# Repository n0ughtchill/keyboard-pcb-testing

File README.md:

# keyboard-pcb-testing

Just learning how to make PCBs

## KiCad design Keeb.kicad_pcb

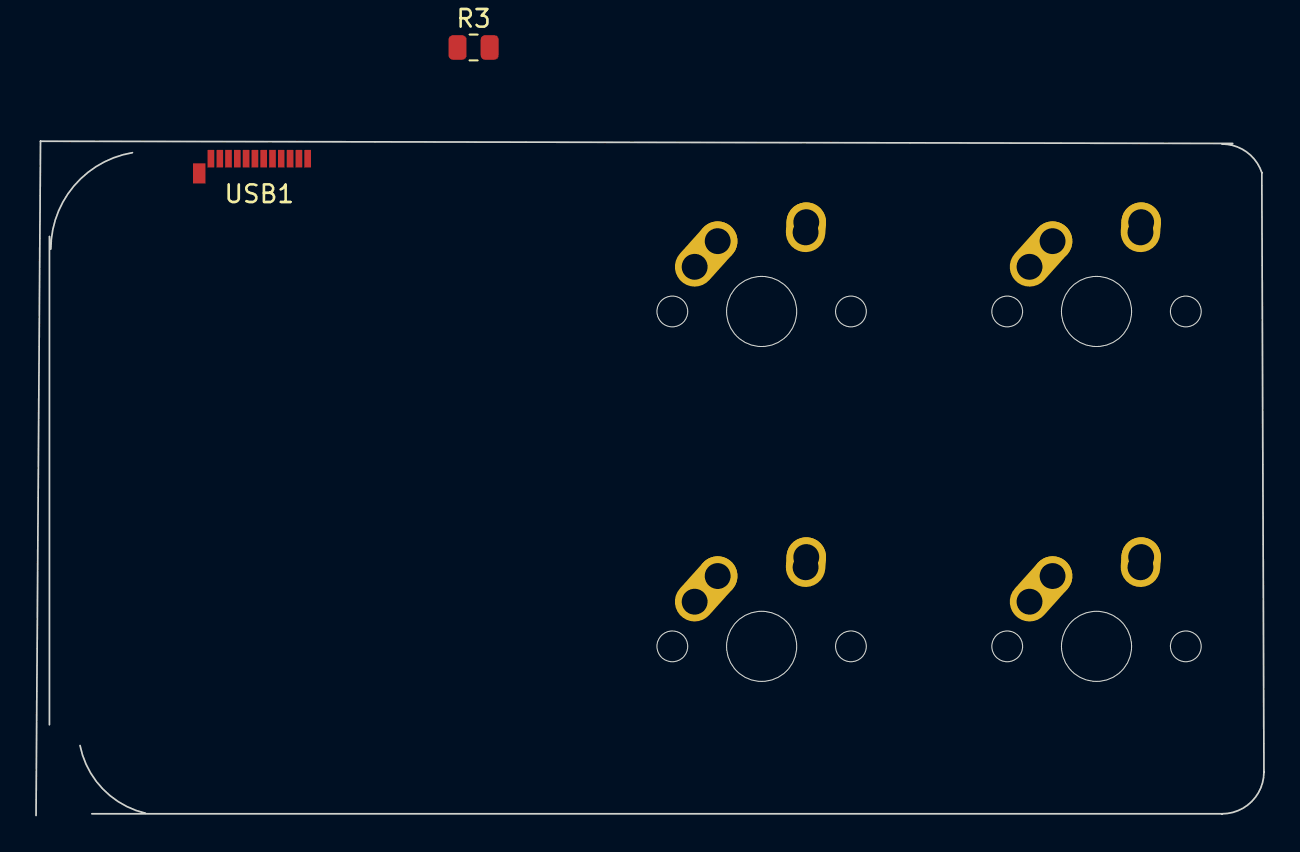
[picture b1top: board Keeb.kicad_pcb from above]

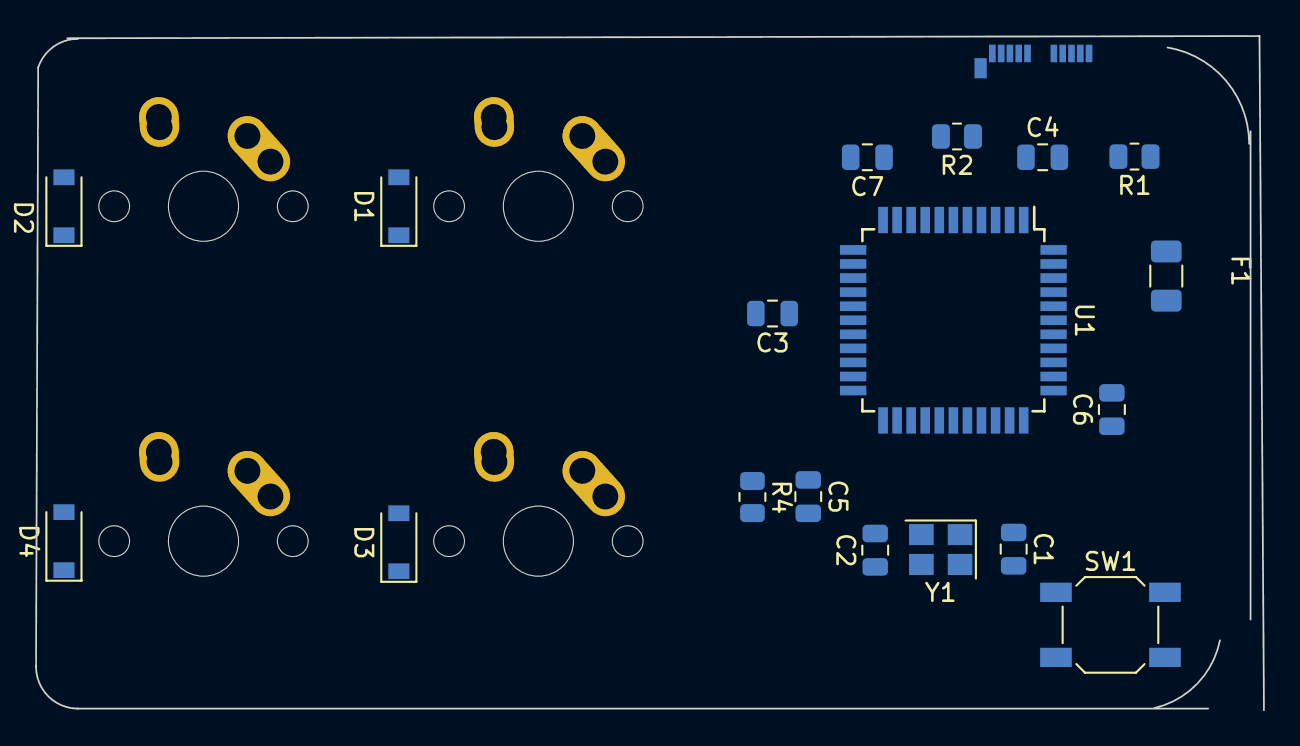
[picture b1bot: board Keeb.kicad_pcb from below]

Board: 2 copper layers, 69.8 x 38.4 mm, 24 parts (18 on the bottom side), 17 nets, no tracks yet.

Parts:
C1, C4, C6: 0.1uF; C_0805_2012Metric
C2, C3: 22pF; C_0805_2012Metric
C5: C_Small; C_0805_2012Metric
C7: 10uF; C_0805_2012Metric
D1, D2, D3, D4: SOD-123; D_SOD-123
F1: 500mA; Fuse_1206_3216Metric
MX1, MX2, MX3, MX4: MX-NoLED; MX-1U-NoLED
R1, R2: 22; R_0805_2012Metric
R3, R4: 10k; R_0805_2012Metric
SW1: SW_Push; SW_SPST_SKQG_WithStem
U1: ATmega32U4-A; TQFP-44_10x10mm_P0.8mm
USB1: Molex-0548190589; USB_C_Plug_Molex_105444
Y1: 16MHz; Crystal_SMD_3225-4Pin_3.2x2.5mm

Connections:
+5V: C1.1, C4.1, C6.1, C7.1, F1.2, U1.2 (UVCC), U1.7 (VBUS), U1.14 (VCC), U1.24 (AVCC), U1.34 (VCC), U1.44 (AVCC)
COL0: MX1.1 (COL), MX2.1 (COL)
COL1: MX3.1 (COL), MX4.1 (COL)
GND: C1.2, C2.1, C3.1, C4.2, C5.2, C6.2, C7.2, R4.2, SW1.1, U1.15 (GND), U1.23 (GND), U1.35 (GND), U1.43 (GND), Y1.2, Y1.4
unnamed: C2.2, U1.17 (XTAL1), Y1.1
unnamed: C3.2, U1.16 (XTAL2), Y1.3
unnamed: C5.1, U1.6 (UCAP)
unnamed: D1.2 (A), MX1.2 (ROW)
unnamed: D2.2 (A), MX2.2 (ROW)
unnamed: D3.2 (A), MX3.2 (ROW)
unnamed: D4.2 (A), MX4.2 (ROW)
unnamed: R1.2, U1.3 (D-)
unnamed: R2.2, U1.4 (D+)
unnamed: R3.2, SW1.2, U1.13 (~RESET)
unnamed: R4.1, U1.33 (~HWB/PE2)
ROW0: D1.1 (K), D3.1 (K)
ROW1: D2.1 (K), D4.1 (K)

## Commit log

2022-07-09 Initial README
2022-07-09 Initialized kiCAD files
2022-07-09 Added submodules
2022-07-09 Added libraries
2022-07-10 basic schema
2022-07-10 added schema footprint
2022-07-10 basic pcb layout
